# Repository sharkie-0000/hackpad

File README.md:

# My Hackpad

hey! this is my hackpad :)

i created this project to practice pcb design, electronics and firmware and at the same time create something i will be able to use on my desk.

the concept of this project is quite easy – small macropad with custom keys, rotary encoder and custom pcb. you can use it to set up your shortcuts, macros, control devices, etc.

## What is it

my hackpad has:

- 9 mechanical switches
- 1 rotary encoder
- XIAO RP2040
- 9 diodes
- 4 mounting holes
- custom PCB
- 3D printed case

i have built almost everything on my own so i would be able to understand the entire process of creating such device.

## Pictures / Files

### 3D Model

### Circuit / Schematic

### PCB Circuit

## Bill of Materials (BOM)

here is the list of parts needed for the hackpad:

Here are the parts used for this build:

| Item                                       | Quantity |      Price | Link                                                                                                                                                                                                                                                                                                                             |
| ------------------------------------------ | -------: | ---------: | -------------------------------------------------------------------------------------------------------------------------------------------------------------------------------------------------------------------------------------------------------------------------------------------------------------------------------- |
| Seeed Studio XIAO RP2040 Development Board |        1 |       ₹589 | [Robu / RoboCraze](https://robocraze.com/products/seeed-studio-xiao-rp2040-development-board?variant=47742255562976&country=IN&currency=INR)                                                                                                                                                                                     |
| Rotary Encoder (PEC12R-4225F-S0024)        |        1 |       ₹159 | [LionCircuits](https://www.lioncircuits.com/parts/PEC12R-4225F-S0024)                                                                                                                                                                                                                                                            |
| Cherry MX Mechanical Switches (Pack of 10) |        9 |       ₹350 | [Cosmic Byte](https://www.thecosmicbyte.com/product/cherry-mx-mechancial-5-pin-switches-compatible-with-hot-swappable-keyboards-pack-of-10/?attribute_pa_switch-type=mx-silent-red)                                                                                                                                              |
| Spongebob Artisan Keycaps                  |        9 |       ₹0 (already have) | [Meckeys](https://meckeys.com/shop/accessories/keyboard-accessories/keycaps/artisan-keycaps/spongebob-artisan-keycaps/)                                                                                                                                                                                                          |
| PCB Fabrication                            |        1 |       ₹720 | [JLCPCB](https://jlcpcb.com)                                                                                                                                                                                                                                                                                                     |
| Diodes                                     |        9 |       ₹149 | [Diode](https://rees52.com/products/100pcs-diode-assortment-kit-rectifier-diode-kit-8-values-diy-electronic-diode?variant=43607283597479&country=IN&currency=INR&utm_medium=product_sync&utm_source=google&utm_content=sag_organic&utm_campaign=sag_organic&srsltid=AfmBOopfW6l_PCFEGSpIn1MzWFSyL2kUMnO_pwWWxPw7mdDOjD9aFjIchQY) |
| 3D Printed Case                            |        1 |          — | —                                                                                                                                                                                                                                                                                                                                |
| **Total Cost**                             |          | **₹1,967** |                                                                                                                                                                                                                                                                                                                                  |

## Assembly Steps

1. Put the PCB on the bottom plate and fix it by using **M3 Screws**.
2. Fasten the upper portion of the box to the bottom plate with the help of **Glue**.
3. The use of M3 screws is **optional**. You can also fasten the whole box with the help of glue.
4. Ensure that everything is properly aligned.

## Why did i build this?

because i wanted to learn to create a circuit board myself rather than always purchasing them off the shelf. a custom macropad seemed to be an engaging way of learning and having something useful that i could use at my desk.

also built for Hack Club because it allowed me to engage in the process of building the circuit board from scratch without letting it stay only in my head.

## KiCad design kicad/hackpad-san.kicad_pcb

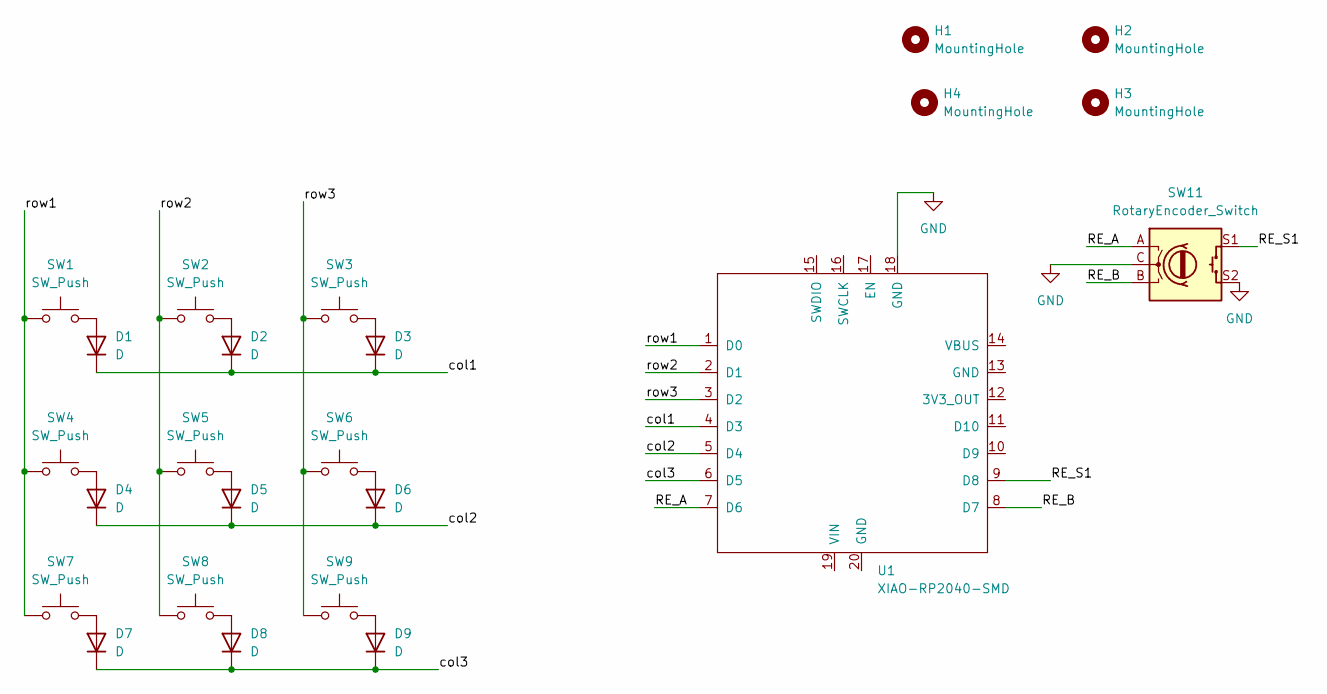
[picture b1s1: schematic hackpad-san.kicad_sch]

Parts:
D1, D2, D3, D4, D5, D6, D7, D8, D9: D; D_DO-35_SOD27_P10.16mm_Horizontal
H1, H2, H3, H4: MountingHole; MountingHole_3.2mm_M3
SW1, SW2, SW3, SW4, SW5, SW6, SW7, SW8, SW9: SW_Push; SW_Cherry_MX_1.00u_PCB
SW11: RotaryEncoder_Switch; RotaryEncoder_Alps_EC11E-Switch_Vertical_H20mm
U1: XIAO-RP2040-SMD

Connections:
/RE_A: SW11.A, U1.7 (D6)
/RE_B: SW11.B, U1.8 (D7)
/RE_S1: SW11.S1, U1.9 (D8)
/col1: D1.1 (K), D2.1 (K), D3.1 (K), U1.4 (D3)
/col2: D4.1 (K), D5.1 (K), D6.1 (K), U1.5 (D4)
/col3: D7.1 (K), D8.1 (K), D9.1 (K), U1.6 (D5)
/row1: SW1.1, SW4.1, SW7.1, U1.1 (D0)
/row2: SW2.1, SW5.1, SW8.1, U1.2 (D1)
/row3: SW3.1, SW6.1, SW9.1, U1.3 (D2)
GND: SW11.C, SW11.S2, U1.18 (GND)
unnamed: D1.2 (A), SW1.2
unnamed: D2.2 (A), SW2.2
unnamed: D3.2 (A), SW3.2
unnamed: D4.2 (A), SW4.2
unnamed: D5.2 (A), SW5.2
unnamed: D6.2 (A), SW6.2
unnamed: D7.2 (A), SW7.2
unnamed: D8.2 (A), SW8.2
unnamed: D9.2 (A), SW9.2

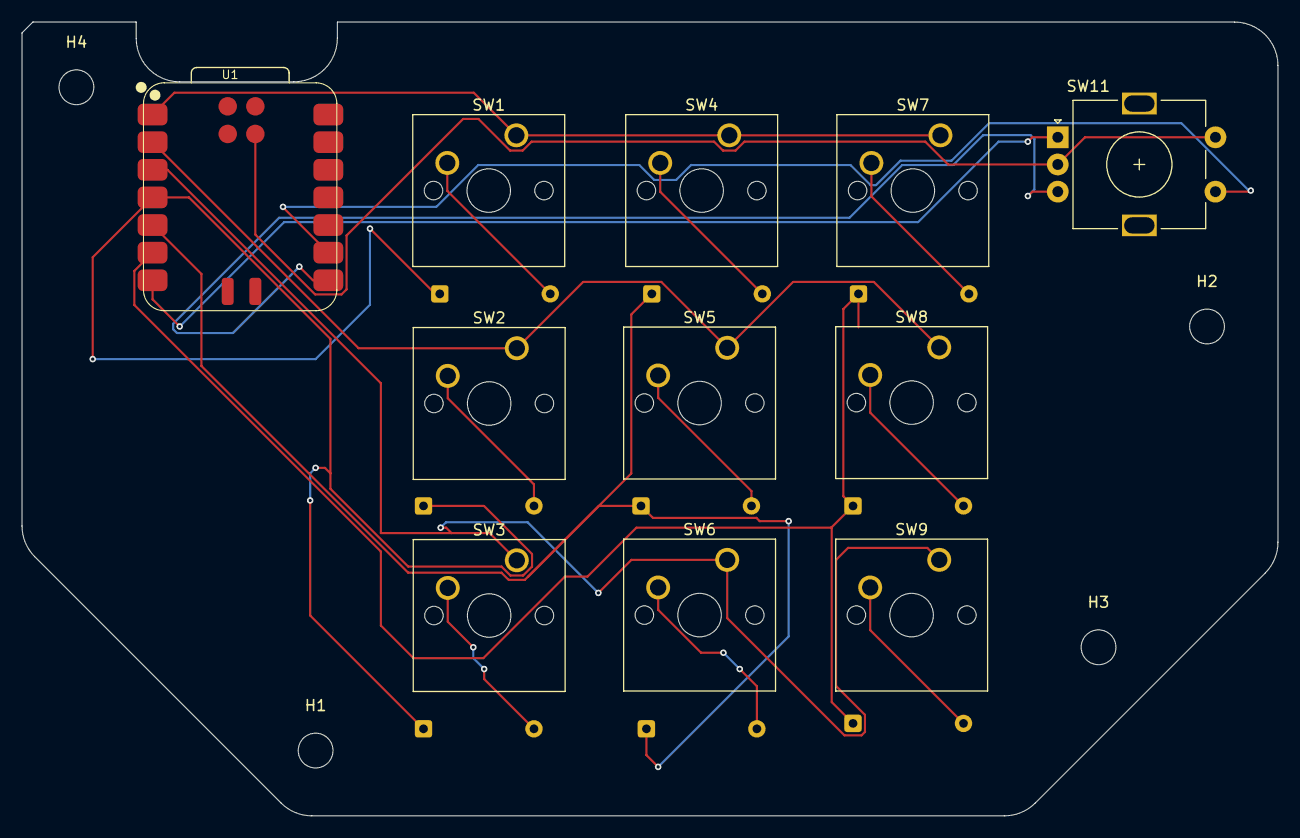
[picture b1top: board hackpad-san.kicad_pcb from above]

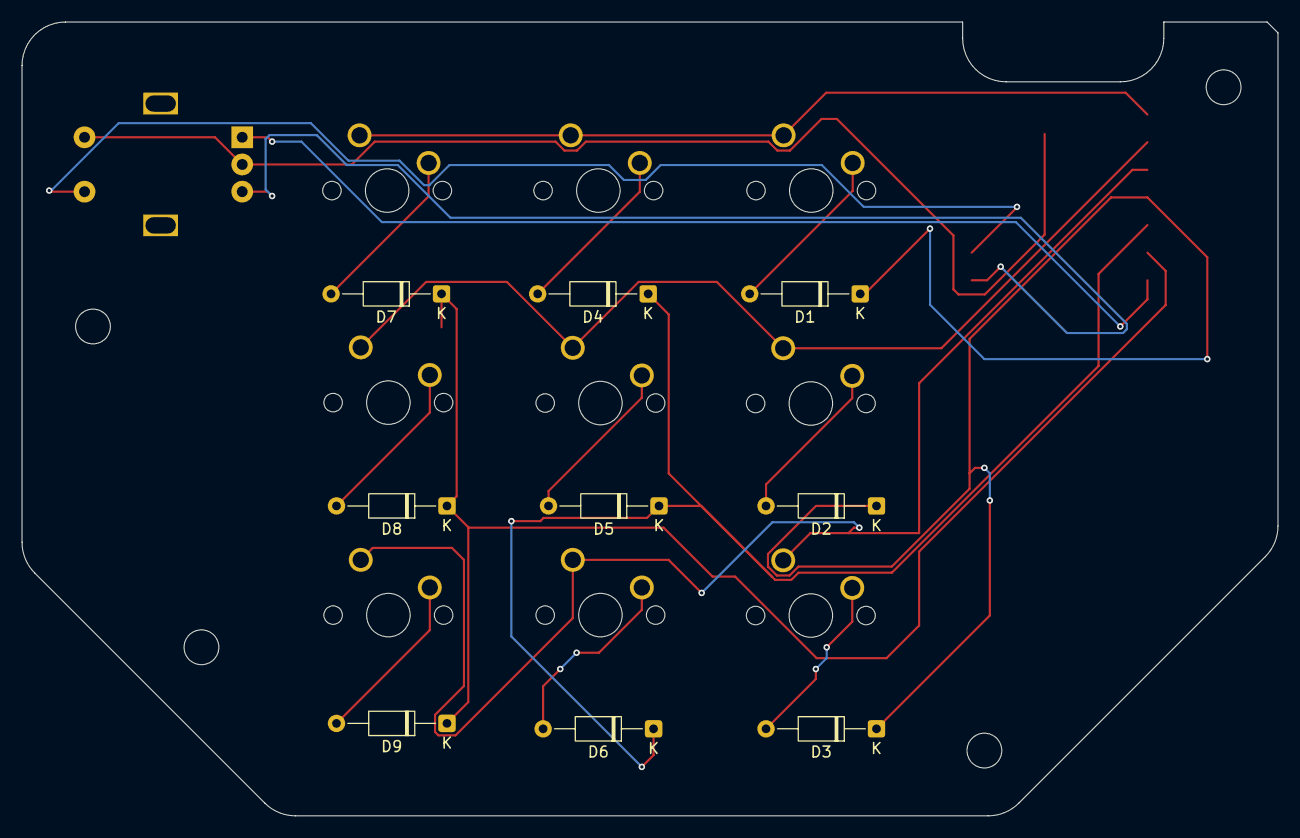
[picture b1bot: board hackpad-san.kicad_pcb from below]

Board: 2 copper layers, 115.5 x 73.0 mm, 24 parts (9 on the bottom side), 19 nets.
